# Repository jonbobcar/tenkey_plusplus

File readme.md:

# Tenkey++

Tenkey++ is a USB-C hotswap numpad with the layout of a standard 10-key. Tenkey++ also has three rotary encoders at the top for additional functionality.

* Keyboard Maintainer: [Jonathon](https://github.com/jonbobcar) :: [jonathon@lizardtrick.com](mailto:jonathon@lizardtrick.com)
* Hardware Source Files: [Tenkey++ GitHub Repository](https://github.com/jonbobcar/tenkey_plusplus)
* Hardware Availability: [Tenkey++ on Tindie](https://www.tindie.com/products/lizardtrick/tenkey/)
* QMK Repo Entry: [QMK Link](https://github.com/qmk/qmk_firmware/tree/master/keyboards/lizard_trick/tenkey_plusplus)

Make example for default layout (set up QMK build environment first):

    make lizard_trick/tenkey_plusplus:default
    
Default Layout:

See the [build environment setup](https://docs.qmk.fm/#/getting_started_build_tools) and the [make instructions](https://docs.qmk.fm/#/getting_started_make_guide) for more information. Brand new to QMK? Start with the [Complete Newbs Guide](https://docs.qmk.fm/#/newbs).

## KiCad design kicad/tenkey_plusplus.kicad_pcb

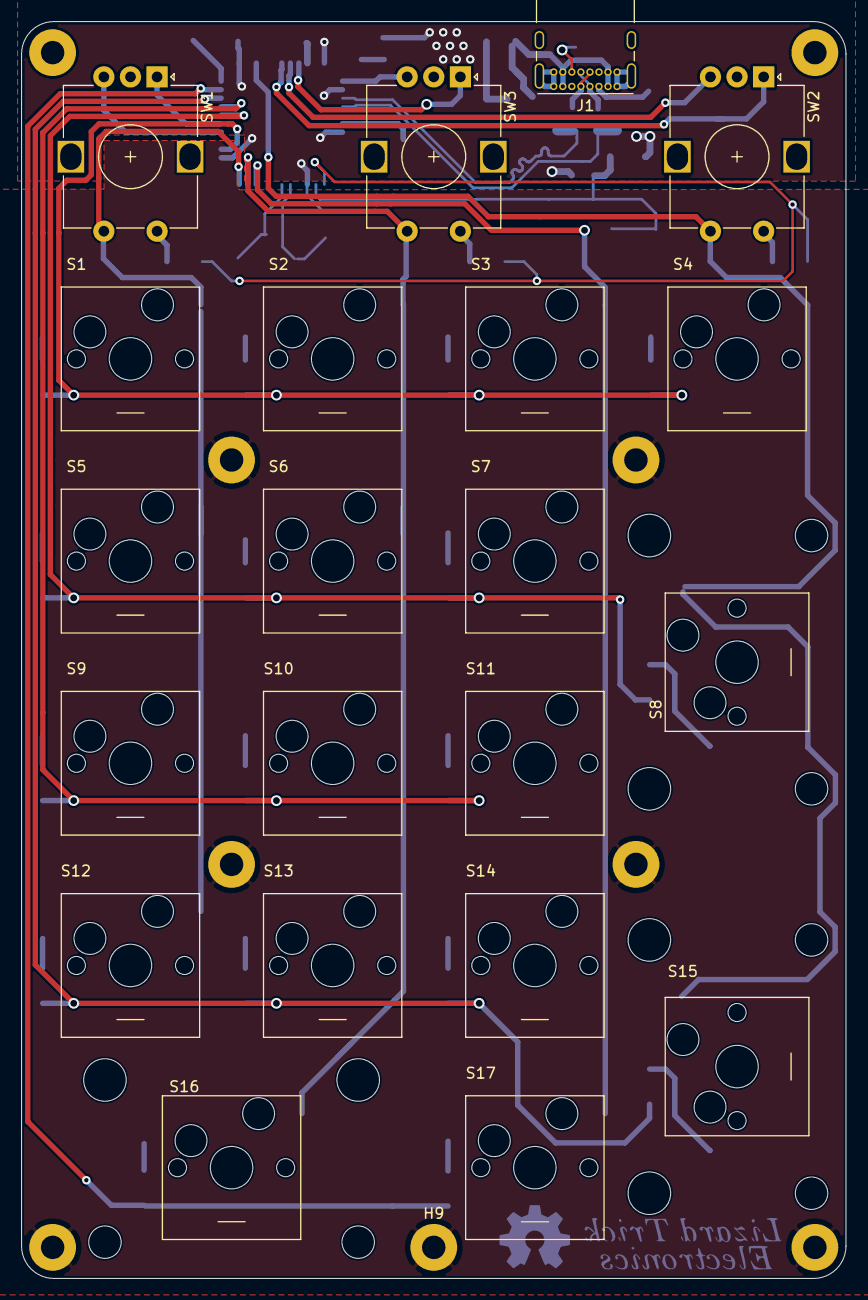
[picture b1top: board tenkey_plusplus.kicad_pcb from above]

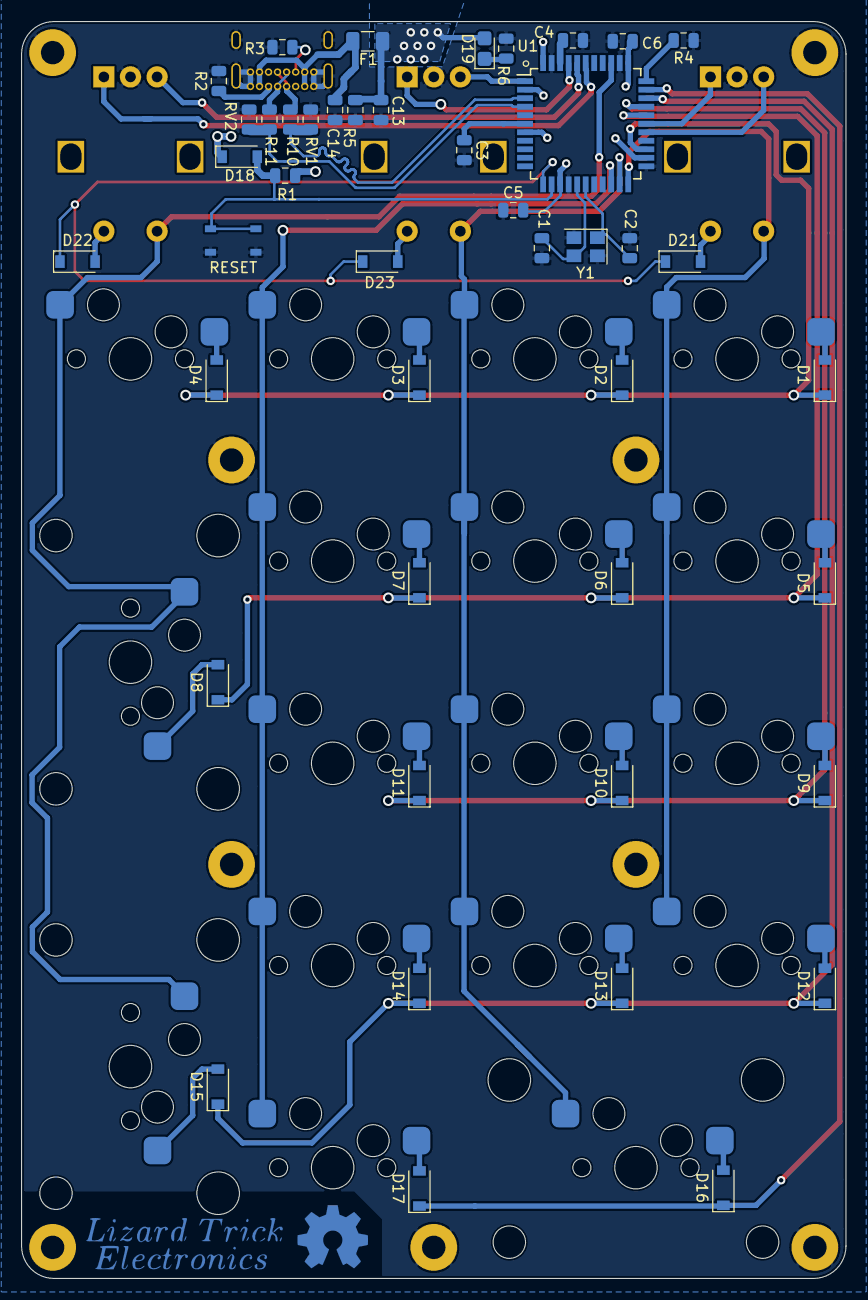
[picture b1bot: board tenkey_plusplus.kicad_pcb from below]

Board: 2 copper layers, 77.5 x 118.1 mm, 79 parts (46 on the bottom side), 52 nets.

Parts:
C1, C2: 22p; C_0805_2012Metric
C3: 1u; C_0805_2012Metric
C4, C5, C6, C13: 100n; C_0805_2012Metric
C14: 22u; C_0805_2012Metric
D1, D2, D3, D4, D5, D6, D7, D8, D9, D10, D11, D12, D13, D14, D15, D16, D17, D18, D21, D22, D23: 1N4148W-7-F; D_SOD-123
D19: LED; LED_0805_2012Metric_Castellated
F1: TR-0603HV500-R; Fuse_1206_3216Metric
H1, H2, H3, H4, H5, H6, H7, H8, H9: MountingHole_Pad; MountingHole_2.2mm_M2_Pad
J1: USB4085-GF-A; USB_C_Receptacle_GCT_USB4085
LOGO1: Lizard_Logo; lizard_trick
LOGO2: Logo_Open_Hardware_Large; OSHW-Symbol_6.7x6mm_Copper
MNT1, MNT2, MNT3: MX_STAB_2U; mx_stab_2u
R1, R4, R5: 10k; R_0805_2012Metric
R2, R3: 5k1; R_0805_2012Metric
R6: 330; R_0805_2012Metric
R10, R11: 22; R_0805_2012Metric
RV1, RV2: CG0603MLC-05E; R_0805_2012Metric
S1, S2, S3, S4, S5, S6, S7, S8, S9, S10, S11, S12, S13, S14, S15, S16, S17: MX_STYLE_SWITCH; hotswap_keyswitch
S18: PTS_810; PTS_180_Tactile_Switch
SW1, SW2, SW3: PEC11R-4220K-S0024; RotaryEncoder_Bourns_PEC11L
U1: ATmega32U4-AU; TQFP-44_10x10mm_P0.8mm
Y1: NX3225SA-16.000M-STD-CSR-1; Crystal_SMD_3225-4Pin_3.2x2.5mm

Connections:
+5V: C5.2, C6.2, C13.2, D18.1, D19.2, F1.2, R1.2, R5.1, U1.2, U1.7, U1.14, U1.24, U1.34, U1.44
COL_0: S1.1, S5.1, S9.1, S12.1, SW1.S2, U1.22
COL_1: S2.1, S6.1, S10.1, S13.1, S16.1, SW3.S2, U1.21
COL_2: S3.1, S7.1, S11.1, S14.1, S17.1, U1.20
COL_3: S4.1, S8.1, S15.1, SW2.S2, U1.36
D+: R11.1, RV2.1, U1.4
D-: R10.1, RV1.1, U1.3
ENC_0_A: SW1.A, U1.28
ENC_0_B: SW1.B, U1.27
ENC_1_A: SW3.A, U1.41
ENC_1_B: SW3.B, U1.1
ENC_2_A: SW2.A, U1.39
ENC_2_B: SW2.B, U1.40
GND: C1.2, C2.2, C3.2, C4.2, C5.1, C6.1, C13.1, C14.2, H1.1, H2.1, H3.1, H4.1, H5.1, H6.1, H7.1, H8.1, H9.1, J1.A1, J1.A12, J1.B1, J1.B12, J1.S1, R2.1, R3.1, R4.1, R5.2, R6.1, RV1.2, RV2.2, S18.1, S18.2, SW1.C, SW2.C, SW3.C, U1.5, U1.15, U1.23, U1.35, U1.43, Y1.2, Y1.4
HSE_IN: C2.1, U1.17, Y1.1
HSE_OUT: C1.1, U1.16, Y1.3
unnamed: C3.1, U1.6
unnamed: C4.1, U1.42
unnamed: C14.1, F1.1, J1.A4, J1.A9, J1.B4, J1.B9
unnamed: D1.2, S1.2
unnamed: D2.2, S2.2
unnamed: D3.2, S3.2
unnamed: D4.2, S4.2
unnamed: D5.2, S5.2
unnamed: D6.2, S6.2
unnamed: D7.2, S7.2
unnamed: D8.2, S8.2
unnamed: D9.2, S9.2
unnamed: D10.2, S10.2
unnamed: D11.2, S11.2
unnamed: D12.2, S12.2
unnamed: D13.2, S13.2
unnamed: D14.2, S14.2
unnamed: D15.2, S15.2
unnamed: D16.2, S16.2
unnamed: D17.2, S17.2
unnamed: D19.1, R6.2
unnamed: D21.2, SW1.S1
unnamed: D22.2, SW2.S1
unnamed: D23.2, SW3.S1
unnamed: J1.A5, R2.2
unnamed: J1.A6, J1.B6, R11.2
unnamed: J1.A7, J1.B7, R10.2
unnamed: J1.B5, R3.2
unnamed: R4.2, U1.33
RESET: D18.2, R1.1, S18.3, S18.4, U1.13
ROW_0: D1.1, D2.1, D3.1, D4.1, U1.25
ROW_1: D5.1, D6.1, D7.1, D8.1, U1.29
ROW_2: D9.1, D10.1, D11.1, U1.30
ROW_3: D12.1, D13.1, D14.1, D15.1, U1.31
ROW_4: D16.1, D17.1, U1.32
ROW_5: D21.1, D22.1, D23.1, U1.12

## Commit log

2020-12-12 Initial Commit
    Committing KiCad and documentation files.
2020-12-12 Added Tindie link to readme
2020-12-29 added QMK link to readme
2020-12-30 adding case and plate .stl files
2021-01-07 updated knurled knob design
2021-07-10 added f3d files for case and plate
2021-07-10 fixed directory issue and moved plate+case to mechanical directory
